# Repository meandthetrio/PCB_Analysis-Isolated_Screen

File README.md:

# PCB Analysis — two unrelated boards in one repo

| Board | Where | Status |
|---|---|---|
| **WavetableController ("Manifold")** — Trey's Daisy Seed synth controller, KiCad 9, fabbed twice | repo root (`WavetableController.*`, `Manifold_Gerb_LedFix/`, `analysis/`) | review complete, rev-2 planning |
| **ProtoBuild1 ("Rev K iron block")** — Quad Eight project, tuned-inductor all-pass "iron" saturation stage, KiCad 10, not yet fabbed | [`boards/ProtoBuild1/`](boards/ProtoBuild1/README.md) | review complete (2026-11-07) |

The two products share nothing but the tooling (`tools/`) and the six-pass checklist. Each has
its own `analysis/` with its own findings ledger (`F-nnn` for Manifold, `PB-F-nnn` for
ProtoBuild1). Everything below this line is about the WavetableController.

---

# PCB Analysis — WavetableController (Daisy Seed synth)

**Read this first.** This folder holds a completed design review of Trey's "WavetableController" board — an Electrosmith Daisy Seed–based wavetable synth controller, 2-layer, 165×102 mm, designed in KiCad 9. The board has been fabbed twice at JLCPCB and the physical boards mostly work. The analysis (all passes complete, 2026-08-13) found several real defects and produced a rev-2 plan.

**If you are Claude opening this fresh:** the authoritative output is [analysis/FINAL_REPORT.md](analysis/FINAL_REPORT.md) (tiered red flags + open questions for Trey), backed by the full findings ledger F-001…F-035 in [analysis/FINDINGS.md](analysis/FINDINGS.md). Do not re-derive anything before checking those. Methodology and which-file-is-truth rules are in [analysis/SOURCE_OF_TRUTH.md](analysis/SOURCE_OF_TRUTH.md).

## Folder contents

| Path | What it is |
|---|---|
| `WavetableController.kicad_pro` / `.kicad_sch` / `.kicad_pcb` | KiCad 9 design files, sent by Trey piecemeal (see provenance below) |
| `Manifold_Gerb_LedFix/` | The Gerbers + drill files actually sent to JLCPCB ("LedFix" round, 2nd proto). **Fab truth for copper.** |
| `ManifoldRe_BOM_NEW - Excel Format.xls` | JLCPCB-format BOM |
| `analysis/` | The full review: FINAL_REPORT, findings ledger, SOURCE_OF_TRUTH, PASS1–6 reports, REV2 OLED plan, routing CSVs extracted from Gerbers, board SVG, parser script. Has its own [README](analysis/README.md) index. |
| `screen mounting solution.md` | Mechanical mounting guide for the rev-2 Crystalfontz CFAL12864G-024W COG OLED (tape+gasket sandwich, plus 3D-printed bezel alternative) |

## Critical provenance warning

Trey sent files reluctantly and in stages: Gerbers+BOM first, then .pro/.sch, then the .kicad_pcb last. File mtimes are transfer times, not edit times. The `.kicad_pcb` in this folder matches the LedFix Gerbers ~97% **but contains NO GND pour** (only 5 keepout zones), while the fabbed B.Cu Gerber has a 164×100 mm filled pour covering 44/63 GND pads. It is a stale/wrong version — **never regenerate Gerbers from this copy.** Standing ask: get Trey's real working .kicad_pcb (the one that shows a filled B.Cu pour when opened). Where sch and pcb disagree (e.g. LED2 wiring), the pcb matches the fabbed boards, so the schematic is the outlier.

## Headline findings (details + evidence in analysis/)

- **Encoder push-buttons dead** — ENCL_CLICK / ENCR_CLICK have zero copper in the Gerbers (floating inputs; ENCR lands on a 3.3V-only Daisy pin). Fab-confirmed.
- **RGB LEDs triple-broken** — LED1/LED2 (CLS6B-FKW) are unplaced (missing from BOM, though the paste stencil expects them), reverse-biased via 300Ω to +9V_FILT (never light either polarity), and three LED pins sit on Daisy's 3.3V-only pins 24/25/30.
- **I2C has zero pull-ups in-design** — the ~203 mm bus relies entirely on the OLED module's onboard pull-ups (open question F-027 for Trey).
- **Duplicate refdes R21** — a layout-only 300Ω footprint at (170.1, 84.8) bridges /OLED_HOT–/+3V3_D in parallel with FB4 (Trey's noise-debug hack, on physical boards, not in schematic). Pick-and-place would put 300Ω where the 10Ω OLED damper belongs; breaks BOM/CPL matching.
- **0.1 mm traces board-wide** — exactly AT JLCPCB's 2-layer 1oz minimum (not below it), zero margin; carries the +3V3_D rail, I2C, SD, MIDI, USB. Recommend 0.2–0.25 mm. DRC min_track_width is 0.0 in the .kicad_pro, so KiCad won't flag them.
- **BOM refdes mismatch** — BOM's S1/S2 don't exist in the schematic (real refs are TAC_SWITCH_1/2, TAC_SHIFT_L1/R1 — note: underscore refs escape `[A-Z]+[0-9]+` regexes).
- 3 marginal fab violations (MK1 annular ring, P2 NPTH clearance, SW1 edge copper — the last is a deliberate notch, accepted). Power design: USB-C is data-only by design; 9V barrel → Schottky bridge → +9V_FILT (~8.3V).

**Open questions blocked on Trey:** F-014 (LED2 sch-vs-pcb, which is intended), F-027 (OLED module pull-up value), and the real .kicad_pcb with the GND pour.

## Rev-2 screen work (planning only, no design files changed)

[analysis/REV2_OLED_PLAN.md](analysis/REV2_OLED_PLAN.md): replace the two HiLetgo SSD1309 modules (boost-coil whine) with bare COG panels on 0.5 mm ZIF, independent I2C addresses 0x3C/0x3D. Two candidate panels:

- **Mono:** Crystalfontz CFAL12864G-024W (2.4", SSD1309) — needs 12.5–13.5V VCC, so a 15V adapter + ~13V LDO. Mounting solved in `screen mounting solution.md`.
- **Greyscale (user's preference):** no 2.42" greyscale panel exists anywhere. Best match is Raystar REX012864U / Winstar WEO012864U — 2.7" SSD1357, 16-level grey, VCC 8–10.5V (12V adapter + 10V LDO). **Unresolved geometry flag:** two 73 mm glasses = 146 mm side-by-side and conflict with the x≈165–200 audio-corridor keep-out. Fallback: stay mono, or 1.54" SSD1327.

Board changes either way: add 2.2k I2C pull-ups, remove J2/FB4/C14/C17/both R21s, use Daisy spare pads 22 & 28 for RES# and VCC_EN sequencing.

## Tooling notes

- **KiCad 9.0.9 (Linux / Claude Code on the web):** `kicad-cli` and the `pcbnew` Python module are on PATH. `.claude/hooks/session-start.sh` (a SessionStart hook) runs `tools/kicad_env_setup.sh` automatically in web sessions; run it by hand with `sudo tools/kicad_env_setup.sh` elsewhere. It installs the stock symbol/footprint libs and seed the user library tables (otherwise ERC/DRC add ~190 "library not found" warnings). `tools/kicad_check.sh [DIR BASENAME]` runs ERC, DRC, netlist, Gerber, SVG and PDF exports into `kicad_out/<basename>/` (git-ignored) as a smoke test; with no arguments it checks the WavetableController. `tools/kicad10_to_9.py SRC DST` makes a KiCad-9-loadable copy of a project that carries KiCad 10 library content (needed for ProtoBuild1).
- **Freerouting 2.4.1 autorouter** is installed by the same setup script (needs Java 25, installed alongside the system Java 21; `freerouting` wrapper on PATH runs it headless with analytics off). `tools/autoroute.py IN.kicad_pcb OUT.kicad_pcb [--passes N]` does DSN export → route → SES import. It temporarily renames the duplicate R21, because the Specctra exporter refuses boards with duplicate refdes (an independent confirmation of that finding). On the stale checked-in board, 2 passes took 53 unrouted connections to 5. Remaining lib warnings name Trey's private libs (`Retroactive_Custom_Parts`, `Jack_3.5mm_CUI_RetroactiveCustom`, `SOP-6_...(RetroactiveCustom)`), which only exist on his machine; footprints are embedded in the `.kicad_pcb`, so they are harmless. Note `pcbnew.LoadBoard(...).Zones()` returns 0 here because the 6 keepout zones live inside footprints, not at board level.
- On Trey's Mac, KiCad 10.0.5 lives at `/Applications/KiCad.app` (kicad-cli at `Contents/MacOS/kicad-cli`; brew cask fails without sudo).
- `analysis/gerber_analyze.py` is the Gerber parser/net-matcher that produced the routing CSVs. Other scratch scripts (pcb_parse.py, pcb_audit.py, DRC/ERC reports) lived in a session scratchpad and may be gone — regenerate from gerber_analyze.py patterns if needed.
- Net names in the routing CSVs are geometrically inferred (anchored at Daisy pins, 6/6 validated on LED nets), not authoritative; `island_*` = unidentified copper.

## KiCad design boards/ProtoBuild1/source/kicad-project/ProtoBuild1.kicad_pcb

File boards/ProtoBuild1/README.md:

# ProtoBuild1 — "Rev K iron block" (Quad Eight project)

**Unrelated to the Manifold / WavetableController board at the repo root.** This folder is a
self-contained design review of a second product that shares only the tooling and the
six-pass checklist.

**If you are Claude opening this fresh:** read `analysis/FINAL_REPORT.md` (tiered red flags +
questions for Trey), backed by the ledger `analysis/FINDINGS.md` (PB-F-001…PB-F-030). Do not
re-derive anything before checking those. Methodology and which-file-is-truth rules are in
`analysis/SOURCE_OF_TRUTH.md`.

## What the board is

A through-hole, 2-layer, 170 × 130 mm, ±15 V audio board: an inductor-saturation ("iron") colour stage, **not an EQ**. The coil sits in a
tuned second-order all-pass (OUT = 2P − D makes the magnitude flat, the phase rotates 360° through
the selected frequency) so the signal current, plus an optional DC magnetising bias, drives the
core into nonlinearity in a chosen band without changing the frequency response
(function derived from the netlist, see PASS5 and PB-F-032). Signal path: input jack → INPUT pot → NE5532 buffer → NE5532 DRIVE
stage (U1A inverting, U1B + U3B followers, 3 × 10 Ω share resistors) → node **D** → Q resistor
(SW2) → node **P** → tuning capacitor (SW1b) → node **X** → coil tap (SW1a) → RM10 tapped
inductor → 1 Ω sense (TP3) → GND. A discrete "Quad Eight" amplifier Q1–Q5 forms OUT = 2P − D,
then a bypass switch, OUTPUT pot, buffer and make-up stage drive the output jack. Q6 is a PNP
current source that can inject DC into X through SW4 to magnetise the core ("iron" bias).
Frequencies 100 / 200 / 400 / 800 Hz (188 / 94 / 47 / 23.5 mH against 13.3 / 6.8 / 3.3 / 1.68 µF).
All panel parts (3 pots, 1 dual pot, 2 rotary switches, 2 toggles) are off-board, wired to 18
screw-terminal blocks. The design has **not been fabricated yet**; JLCPCB is the intended fab.

## Folder contents

| Path | What it is |
|---|---|
| `source/` | The upload `ProtoBuild1-autorouted.zip` (7 Nov 2026) unpacked verbatim. `source/README-from-upload.md` is the author's own file list. |
| `source/kicad-project/` | `ProtoBuild1.kicad_sch`, `ProtoBuild1.kicad_pcb` (KiCad 8 file header, no zone fill), `ProtoBuild1-zones-filled-kicad10-format.kicad_pcb` (native KiCad 10 save, zone fill stored — **the file the Gerbers came from**), custom coil symbol + two footprints, project lib tables. |
| `source/gerbers/` | 7 Gerber layers + Excellon drill + job file, plotted by KiCad 10.0.8 on 2026-11-07. Candidate fab set, verified identical to the board file (Pass 0). |
| `source/reports/` | The author's KiCad 10 ERC / DRC text reports and the KiCad 10 netlist. |
| `source/ProtoBuild1-parts-list.xlsx` | Parts list with manufacturer numbers, DigiKey stock/prices (7 Nov 2026), and a "Trey has" column to fill in. |
| `analysis/` | The review: FINAL_REPORT, findings ledger, SOURCE_OF_TRUTH, pass plan, PASS0–6 reports, thresholds, extraction scripts, datasheet text extracts. |

## Opening the design files — read before you try

The `.kicad_sch` and `ProtoBuild1.kicad_pcb` are **not** KiCad 8 files despite their headers:
they are script-assembled from KiCad 10 library content. KiCad 10 opens them; **KiCad 9.0.9
refuses both with a parse error** (finding PB-F-001). In a KiCad 9 session run

```
tools/kicad10_to_9.py boards/ProtoBuild1/source/kicad-project kicad_out/pb1_conv
tools/kicad_check.sh kicad_out/pb1_conv ProtoBuild1
```

which writes a loadable *copy* (documented token strips only; copper and nets untouched, verified
by `analysis/scripts/gerber_vs_pcb.py`). Never edit the copy as if it were the design.

## Headline findings (details and evidence in analysis/)

- **The inductor is not connected** on the uploaded board: the coil footprint's 12 pins and its
  breakout row carry no net (PB-F-018). **Decision 2026-11-08:** the coil moves to a plug-in
  daughterboard; the main board needs a keyed 1 × 5 header for common + four taps (PB-F-031).
- **TO-92 pads break the JLCPCB annular-ring minimum** (0.15 mm vs 0.18 mm absolute minimum) on
  all 9 pads of Q1–Q3, because the 1.27 mm-pitch `TO-92_Inline` footprint was used while the BOM
  specifies 2.54 mm formed-lead parts (PB-F-006).
- **BOM is short two terminal blocks** (J13 3-pos and J17 2-pos, the coil-lead blocks); the "41
  terminal positions" wiring plan should be 46 (PB-F-020).
- **KiCad version trap** — files only open in KiCad 10; the upload README says 9 or 10
  (PB-F-001). DRC constraints are empty in the project file, so the author's "DRC 0" only
  reflects the 0.2 mm netclass (PB-F-002).
- **Q6 bias current source** can reach ~80 mA / ~0.85 W, above the BOM's "50 mA / 0.6 W", and
  its slip-on heatsink has ~6 mm of clearance where the BOM asks for 10 mm (PB-F-015, PB-F-023).
- Copper, netlist and Gerbers are mutually consistent (100 % segment match, 57/57 nets), ERC has
  zero errors in KiCad 9 and 10, polarities and transistor pinouts all check out against the
  datasheets, every terminal block faces outward at an edge, and the tuning arithmetic lands on
  100.7 / 199 / 404 / 801 Hz.

**Open questions for Trey:** the coil's actual pin layout (Don-Audio drawing), whether the
mounting holes should bond to chassis ground, heatsink orientation on Q6, and which KiCad
version the working files will live in.

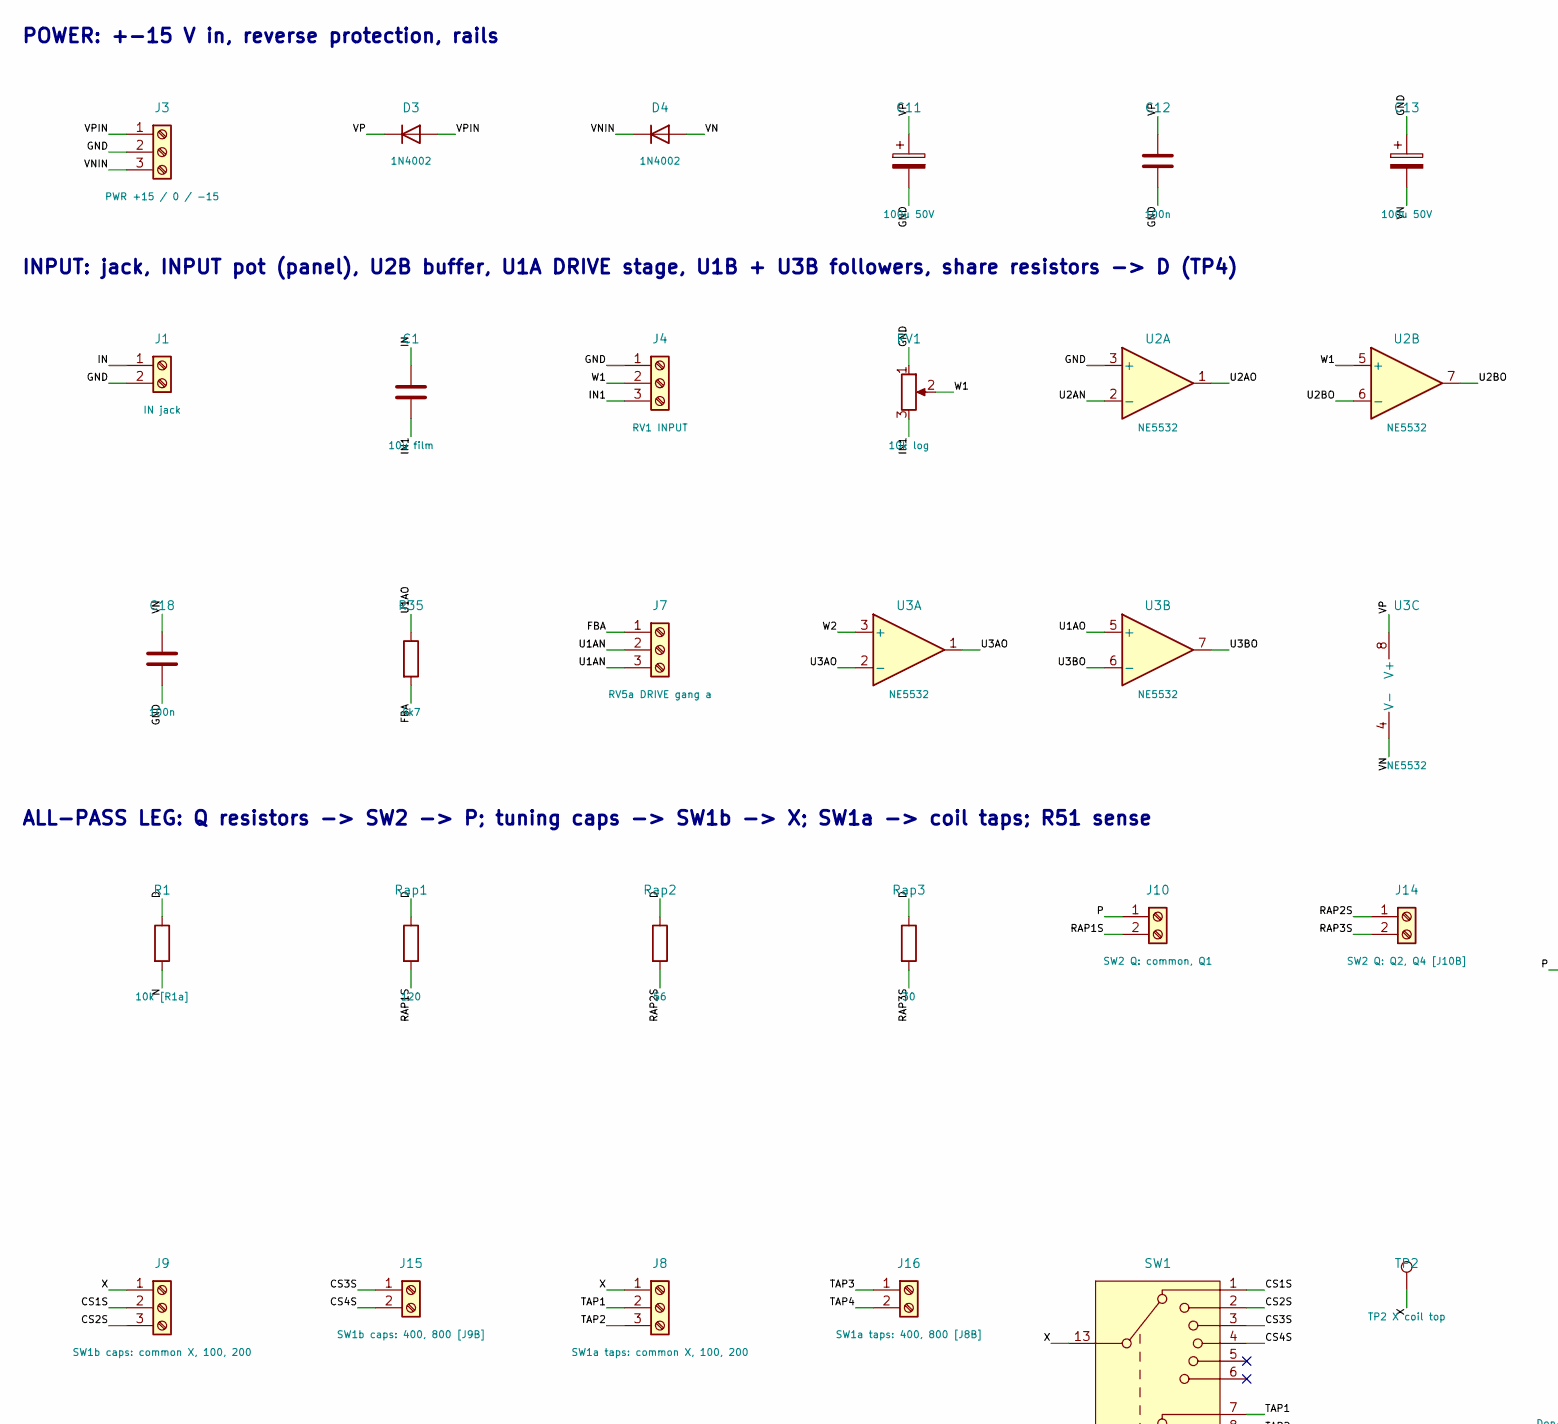
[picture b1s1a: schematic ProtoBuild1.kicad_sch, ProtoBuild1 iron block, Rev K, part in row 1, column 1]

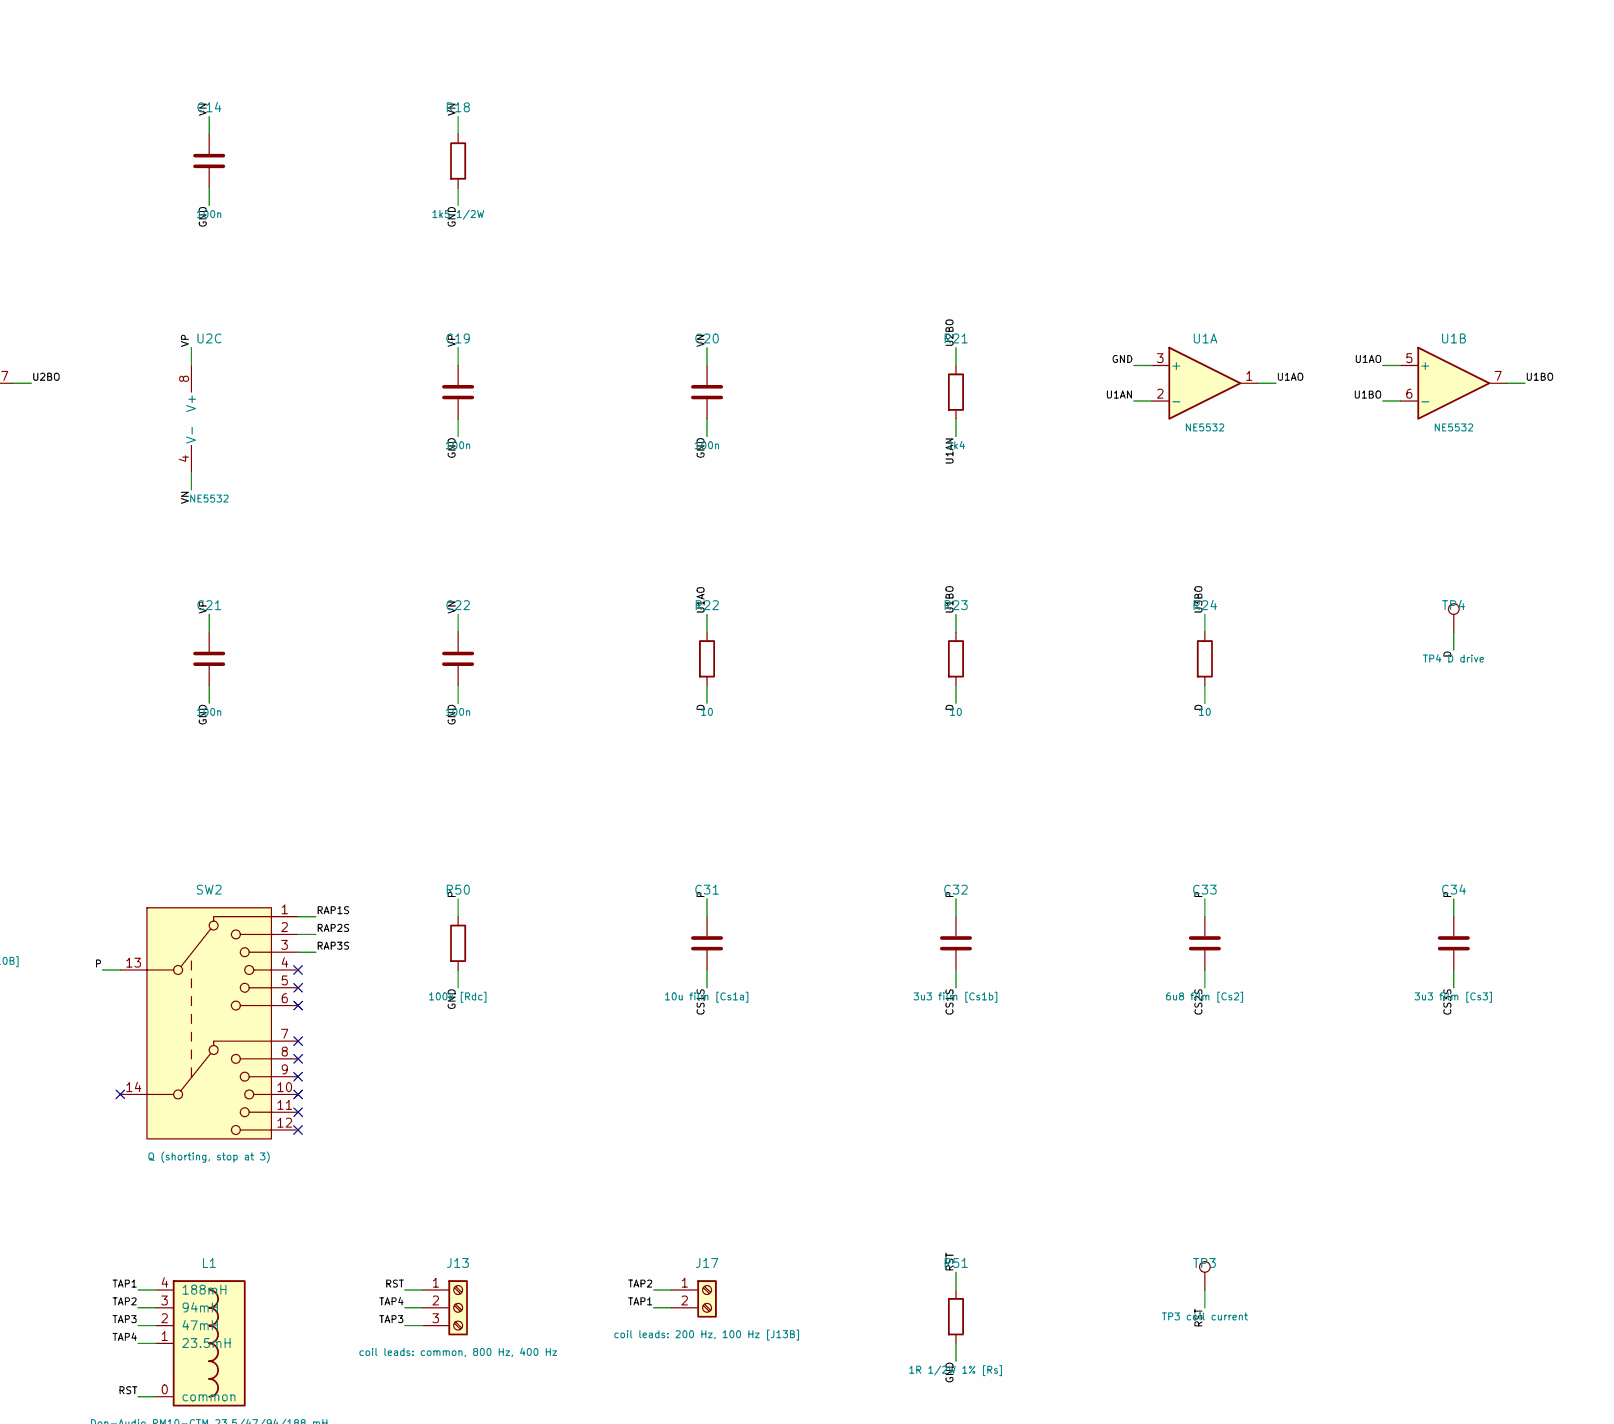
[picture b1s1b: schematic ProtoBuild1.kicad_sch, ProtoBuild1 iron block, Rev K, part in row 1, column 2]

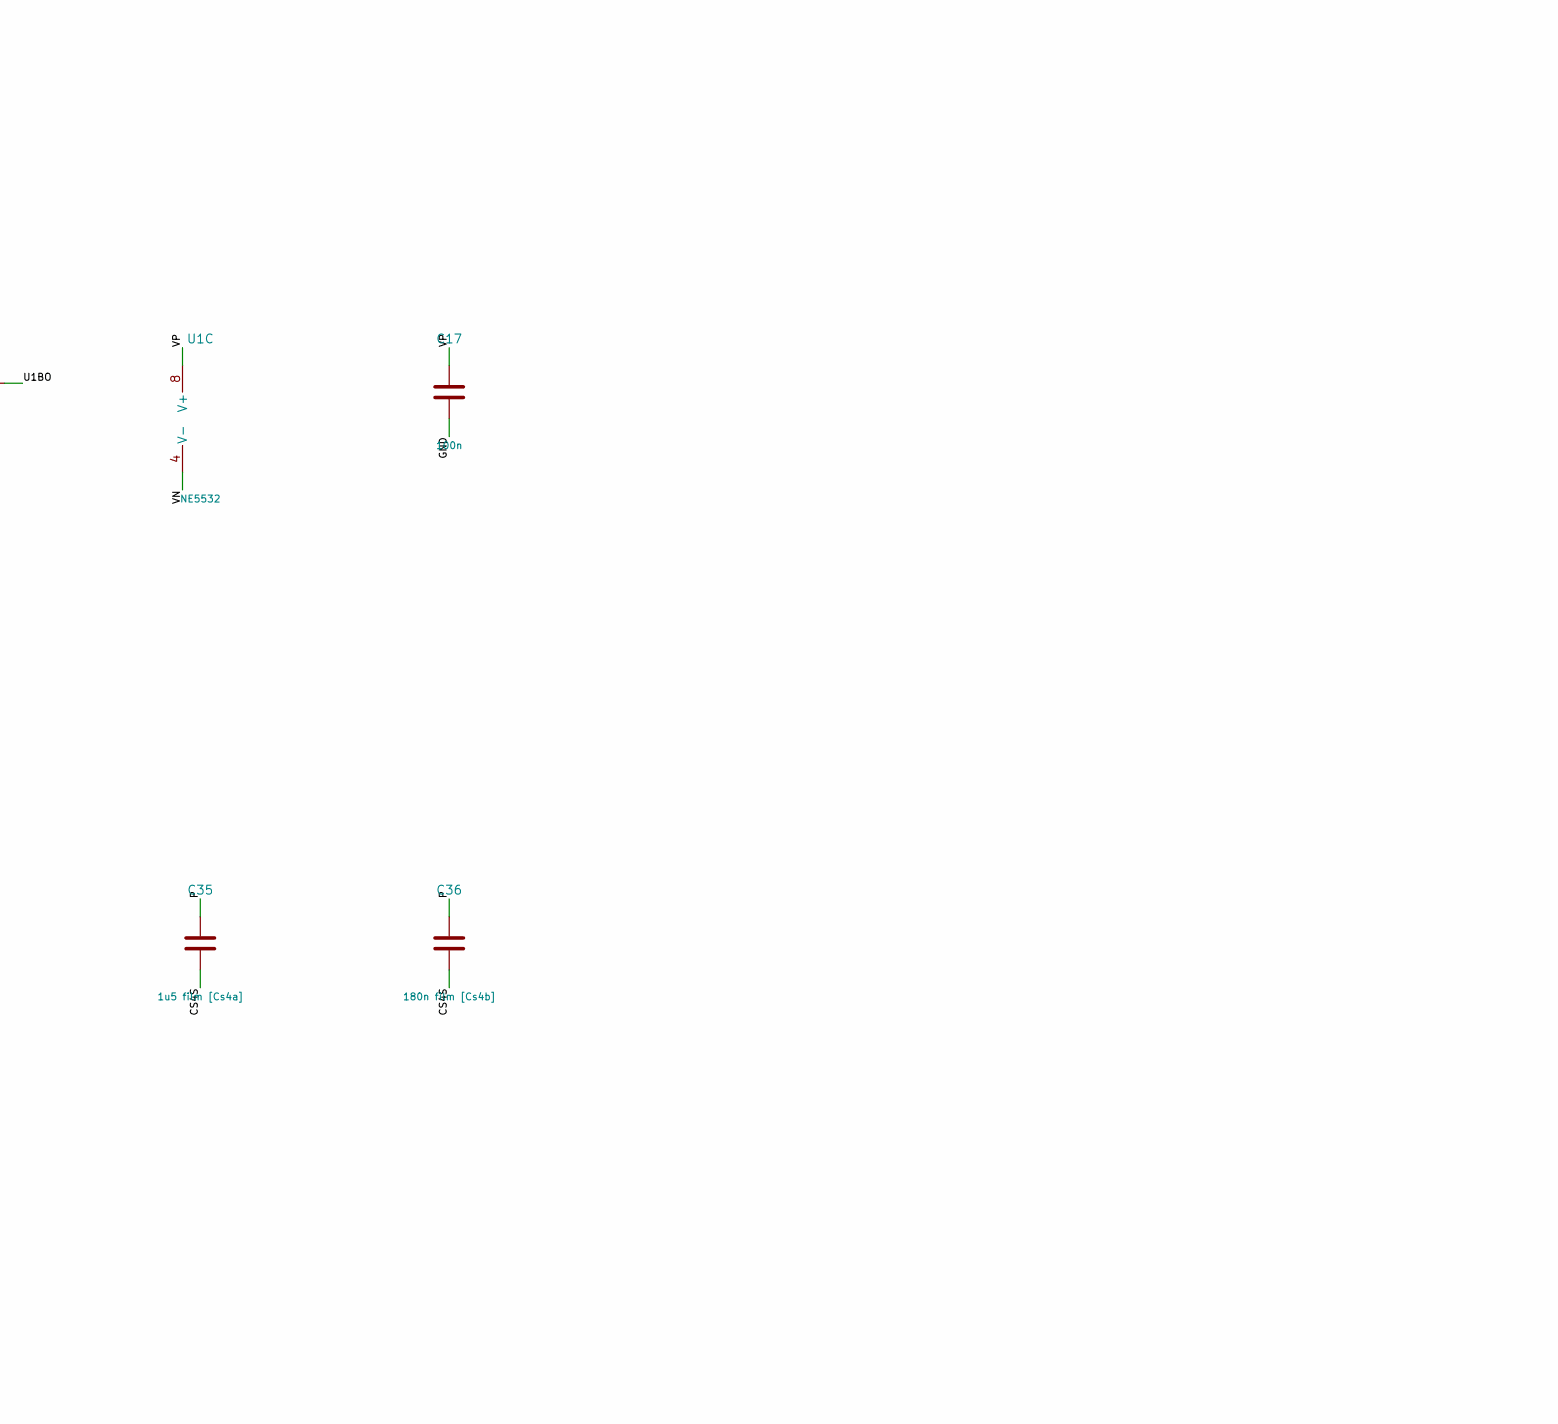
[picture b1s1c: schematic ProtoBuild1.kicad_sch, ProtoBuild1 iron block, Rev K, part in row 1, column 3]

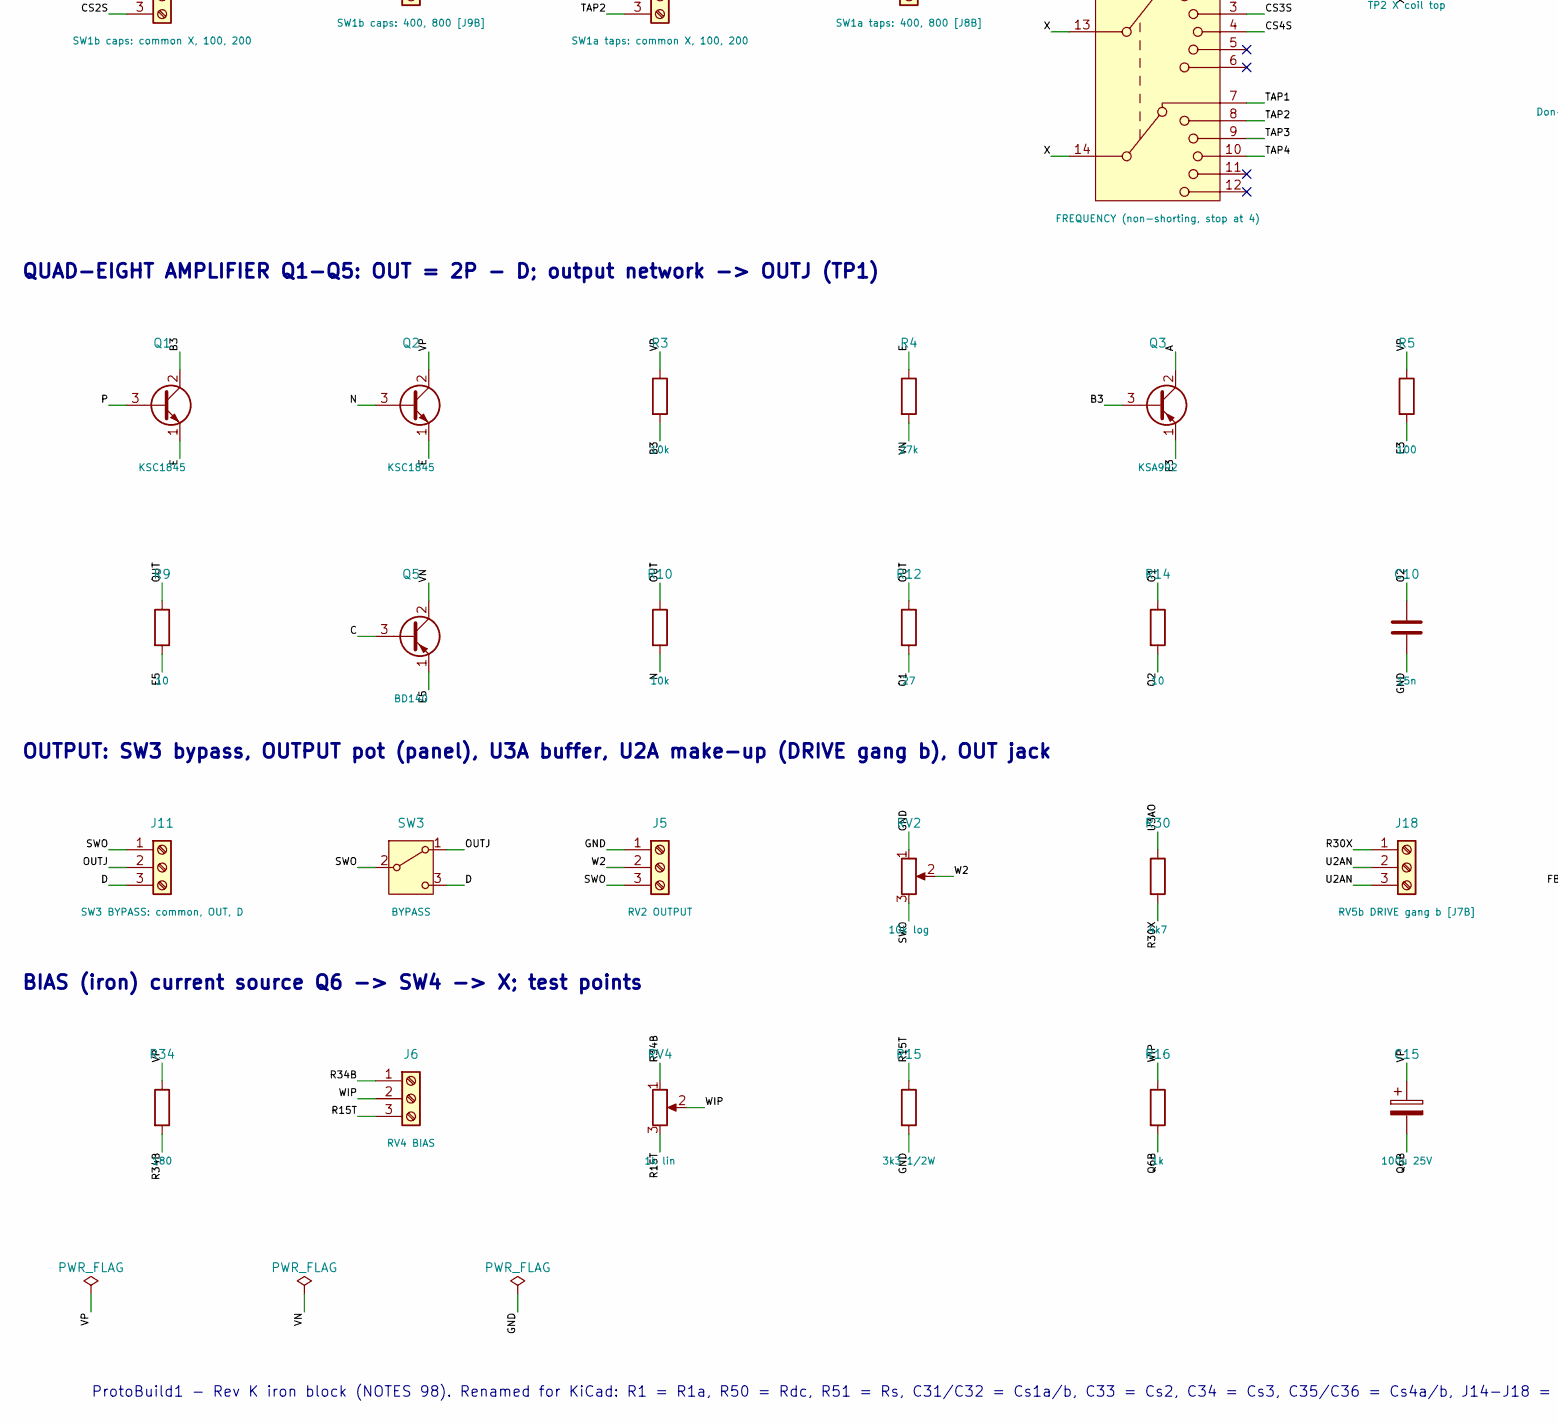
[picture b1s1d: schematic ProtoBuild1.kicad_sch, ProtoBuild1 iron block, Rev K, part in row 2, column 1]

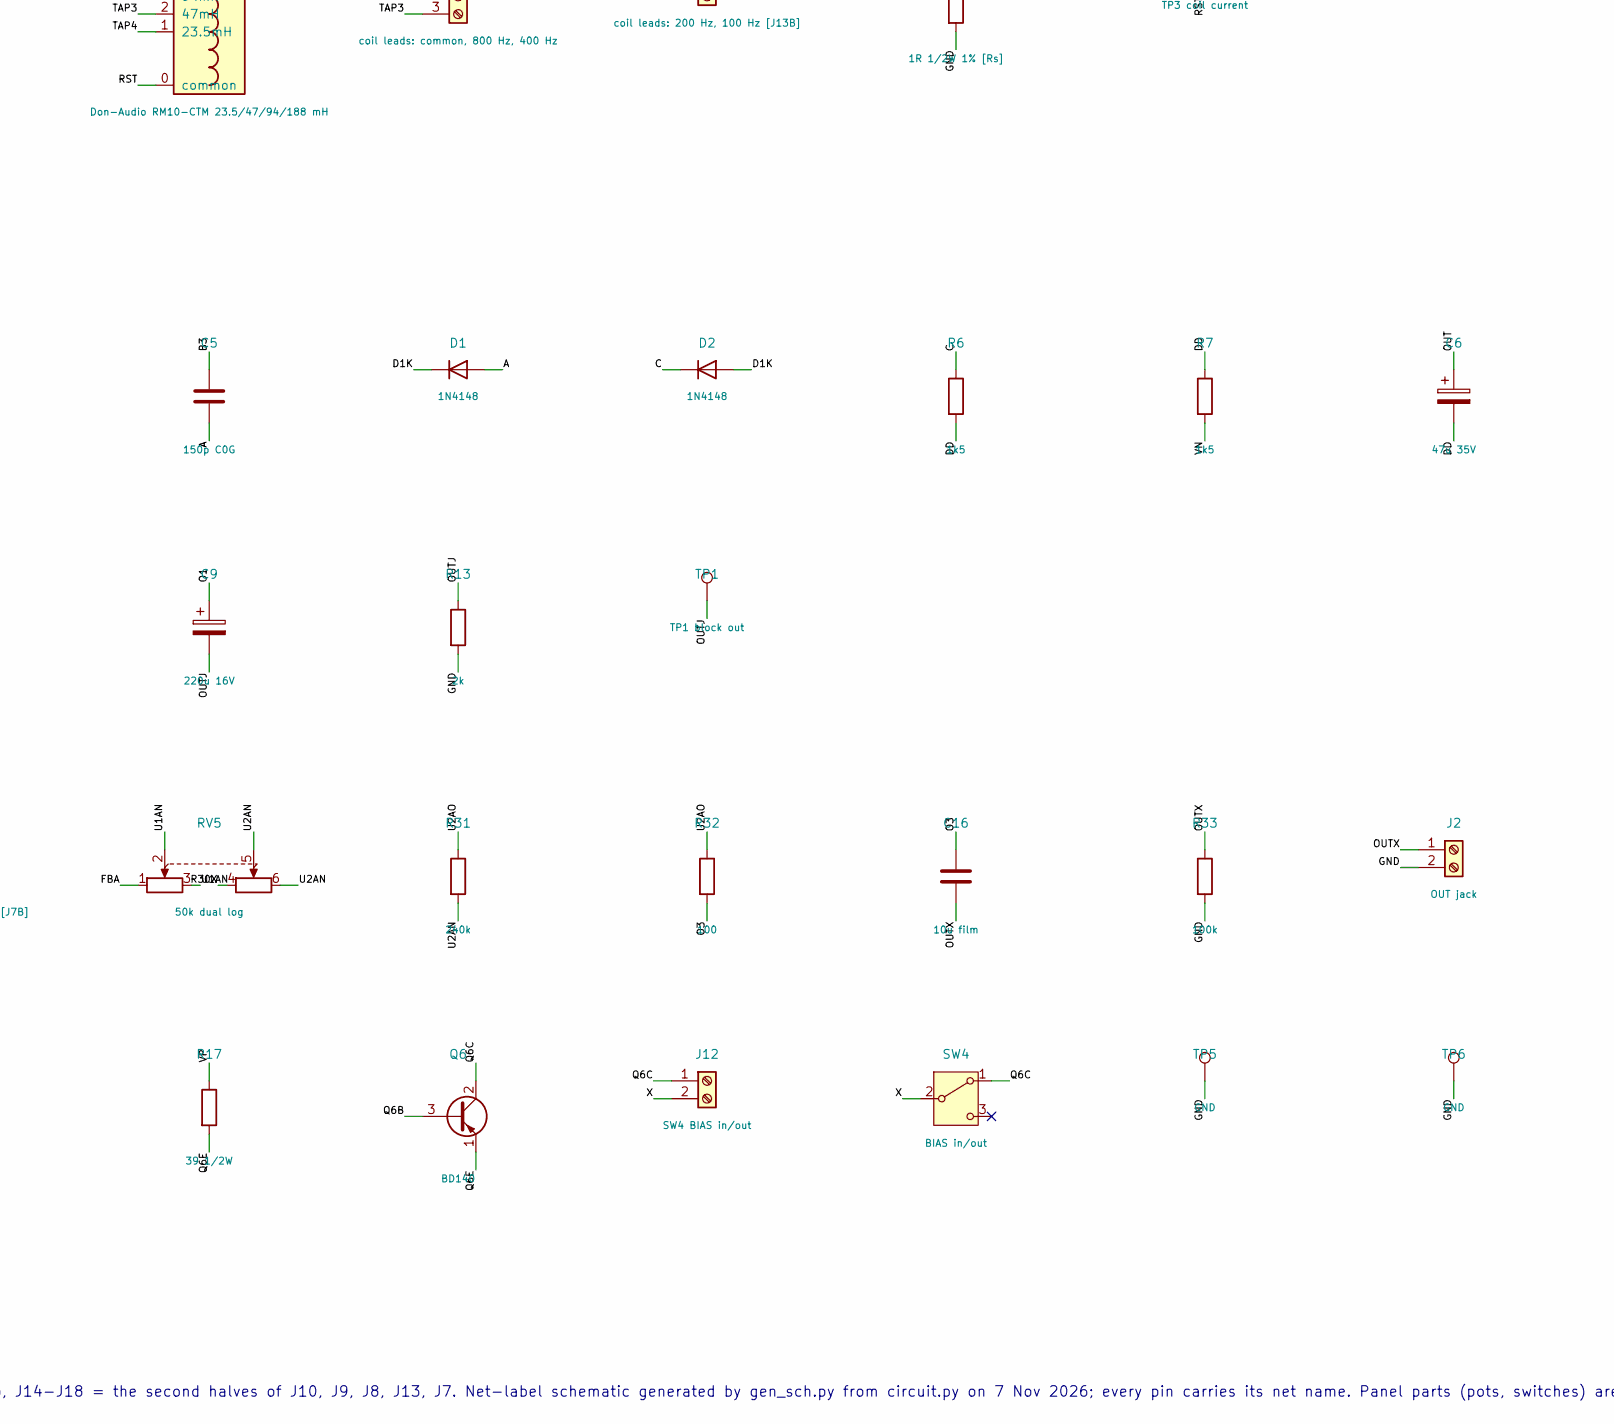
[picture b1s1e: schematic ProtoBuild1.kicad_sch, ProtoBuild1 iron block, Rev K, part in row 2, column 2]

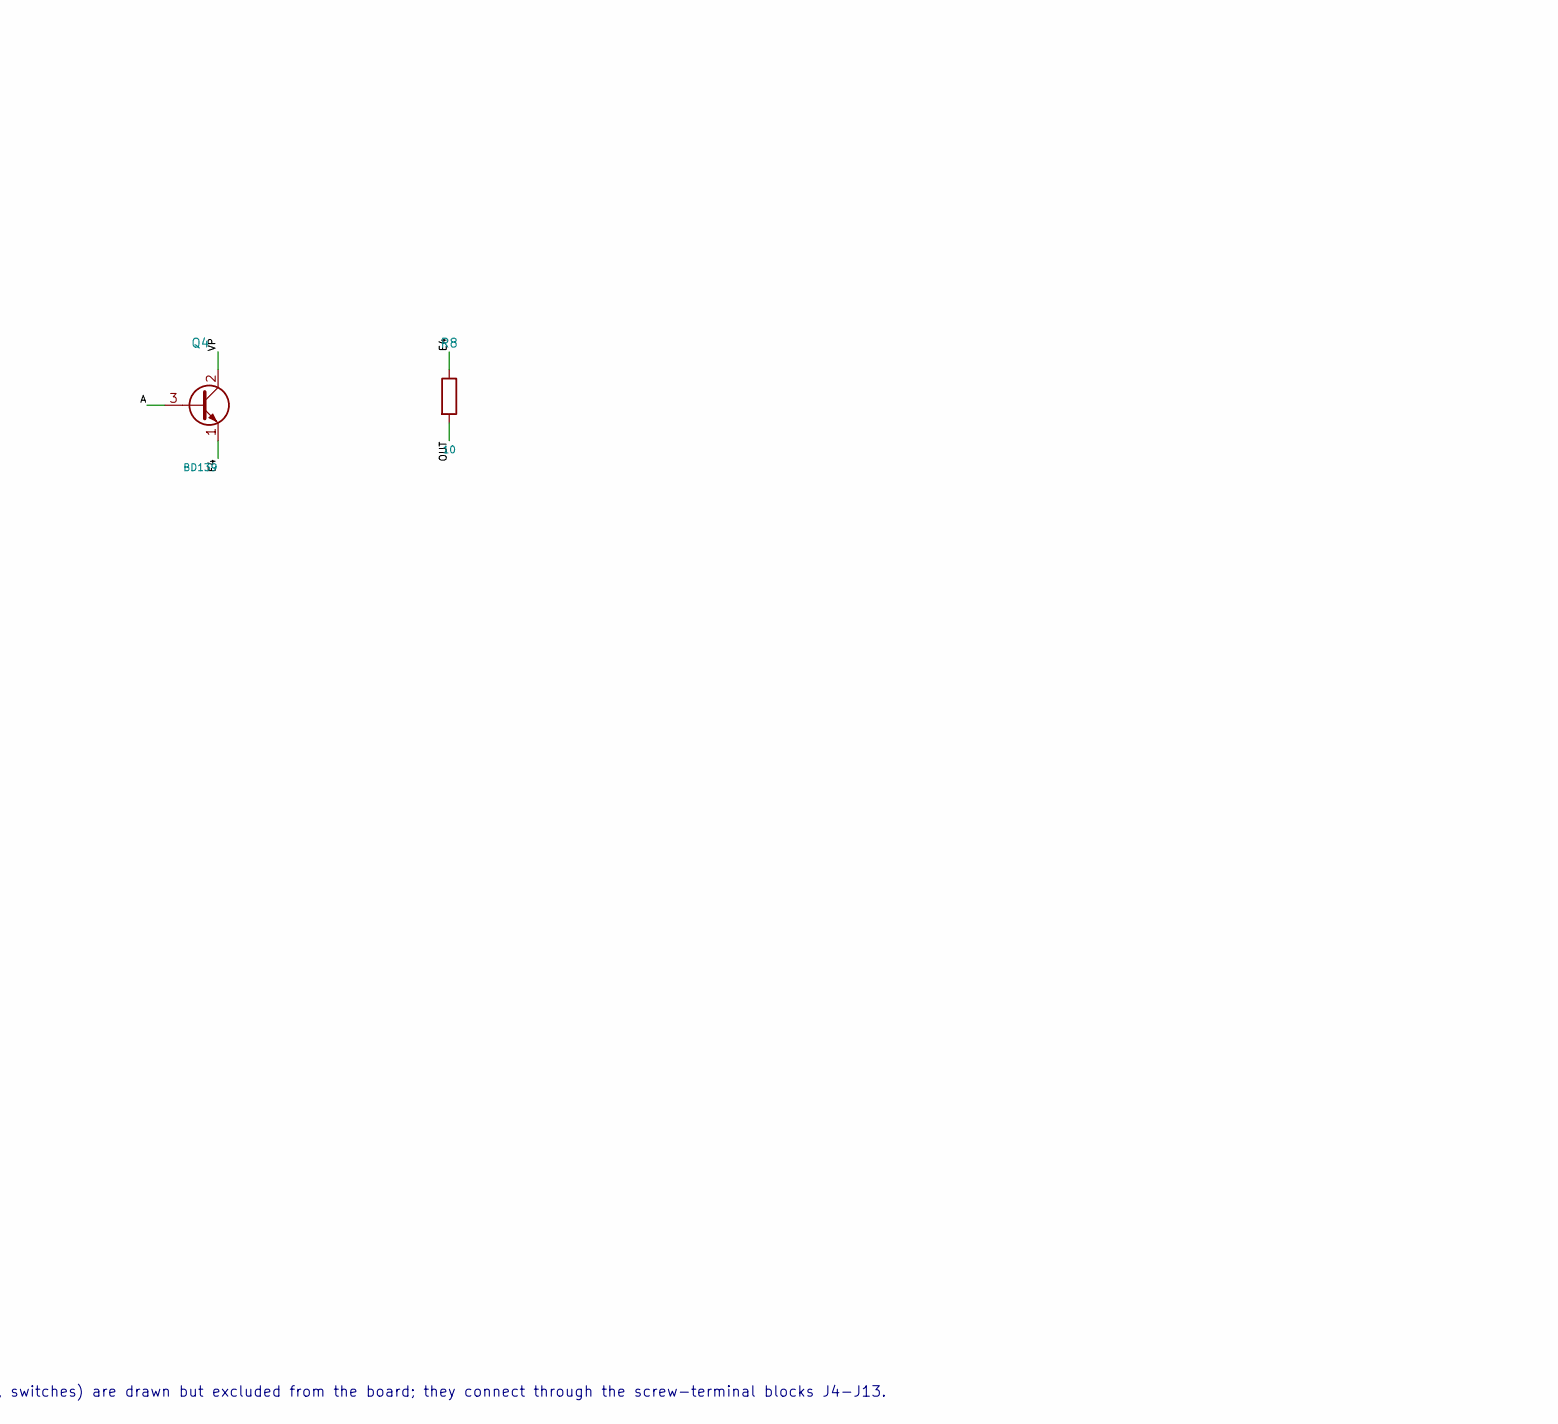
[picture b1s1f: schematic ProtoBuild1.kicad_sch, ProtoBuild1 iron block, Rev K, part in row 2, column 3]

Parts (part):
C1, C16: 10u film; C_Rect_L26.5mm_W11.5mm_P22.50mm_MKS4; MPN ECQ-E1106KF
C5: 150p C0G; C_Disc_D3.0mm_W1.6mm_P2.50mm; MPN K151J15C0GF5TL2
C6: 47u 35V; CP_Radial_D6.3mm_P2.50mm; MPN EEU-FM1V470
C9: 220u 16V; CP_Radial_D8.0mm_P3.50mm; MPN UPW1C221MPD
C10: 15n; C_Rect_L7.2mm_W2.5mm_P5.00mm; MPN B32529C0153J000
C11, C13: 100u 50V; CP_Radial_D8.0mm_P3.50mm; MPN UPW1H101MPD
C12, C14, C17, C18, C19, C20, C21, C22: 100n; C_Rect_L7.2mm_W2.5mm_P5.00mm; MPN B32529C0104J000
C15: 100u 25V; CP_Radial_D6.3mm_P2.50mm; MPN UPW1E101MED
C31: 10u film [Cs1a]; C_Rect_L26.5mm_W11.5mm_P22.50mm_MKS4; MPN ECQ-E1106KF
C32: 3u3 film [Cs1b]; C_Rect_L18.0mm_W9.0mm_P15.00mm_FKS3_FKP3; MPN ECQ-E1335KF
C33: 6u8 film [Cs2]; C_Rect_L26.5mm_W8.5mm_P22.50mm_MKS4; MPN ECQ-E1685KF
C34: 3u3 film [Cs3]; C_Rect_L18.0mm_W9.0mm_P15.00mm_FKS3_FKP3; MPN ECQ-E1335KF
C35: 1u5 film [Cs4a]; C_Rect_L18.0mm_W6.0mm_P15.00mm_FKS3_FKP3; MPN ECQ-E1155KF
C36: 180n film [Cs4b]; C_Rect_L11.5mm_W5.0mm_P10.00mm_MKT; MPN ECQ-E2184KF
D1, D2: 1N4148; D_DO-35_SOD27_P7.62mm_Horizontal; MPN 1N4148
D3, D4: 1N4002; D_DO-41_SOD81_P10.16mm_Horizontal; MPN 1N4002G
J1: IN jack; TerminalBlock_Phoenix_MKDS-1,5-2-5.08_1x02_P5.08mm_Horizont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; MPN Phoenix 1715022
J2: OUT jack; TerminalBlock_Phoenix_MKDS-1,5-2-5.08_1x02_P5.08mm_Horizont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; MPN Phoenix 1715022
J3: PWR +15 / 0 / -15; TerminalBlock_Phoenix_MKDS-1,5-3-5.08_1x03_P5.08mm_Horizont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; MPN Phoenix 1715035
J4: RV1 INPUT; TerminalBlock_Phoenix_MKDS-1,5-3-5.08_1x03_P5.08mm_Horizont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; MPN Phoenix 1715035
J5: RV2 OUTPUT; TerminalBlock_Phoenix_MKDS-1,5-3-5.08_1x03_P5.08mm_Horizont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; MPN Phoenix 1715035
J6: RV4 BIAS; TerminalBlock_Phoenix_MKDS-1,5-3-5.08_1x03_P5.08mm_Horizont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; MPN Phoenix 1715035
J7: RV5a DRIVE gang a; TerminalBlock_Phoenix_MKDS-1,5-3-5.08_1x03_P5.08mm_Horizont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; MPN Phoenix 1715035
J8: SW1a taps: common X, 100, 200; TerminalBlock_Phoenix_MKDS-1,5-3-5.08_1x03_P5.08mm_Horizont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; MPN Phoenix 1715035
J9: SW1b caps: common X, 100, 200; TerminalBlock_Phoenix_MKDS-1,5-3-5.08_1x03_P5.08mm_Horizont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; MPN Phoenix 1715035
J10: SW2 Q: common, Q1; TerminalBlock_Phoenix_MKDS-1,5-2-5.08_1x02_P5.08mm_Horizont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; MPN Phoenix 1715022
J11: SW3 BYPASS: common, OUT, D; TerminalBlock_Phoenix_MKDS-1,5-3-5.08_1x03_P5.08mm_Horizont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; MPN Phoenix 1715035
J12: SW4 BIAS in/out; TerminalBlock_Phoenix_MKDS-1,5-2-5.08_1x02_P5.08mm_Horizont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; MPN Phoenix 1715022
J13: coil leads: common, 800 Hz, 400 Hz; TerminalBlock_Phoenix_MKDS-1,5-3-5.08_1x03_P5.08mm_Horizont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; MPN Phoenix 1715035
J14: SW2 Q: Q2, Q4 [J10B]; TerminalBlock_Phoenix_MKDS-1,5-2-5.08_1x02_P5.08mm_Horizont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; MPN Phoenix 1715022
J15: SW1b caps: 400, 800 [J9B]; TerminalBlock_Phoenix_MKDS-1,5-2-5.08_1x02_P5.08mm_Horizont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; MPN Phoenix 1715022
J16: SW1a taps: 400, 800 [J8B]; TerminalBlock_Phoenix_MKDS-1,5-2-5.08_1x02_P5.08mm_Horizont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; MPN Phoenix 1715022
J17: coil leads: 200 Hz, 100 Hz [J13B]; TerminalBlock_Phoenix_MKDS-1,5-2-5.08_1x02_P5.08mm_Horizont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; MPN Phoenix 1715022
J18: RV5b DRIVE gang b [J7B]; TerminalBlock_Phoenix_MKDS-1,5-3-5.08_1x03_P5.08mm_Horizont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; MPN Phoenix 1715035
L1: Don-Audio RM10-CTM 23.5/47/94/188 mH; RM10_corner_12P_breakout; MPN Don-Audio RM10-CTM
Q1, Q2: KSC1845; TO-92_Inline; MPN KSC1845FTA
Q3: KSA992; TO-92_Inline; MPN KSA992FTA
Q4: BD139; TO-126-3_Vertical; MPN BD139G
Q5, Q6: BD140; TO-126-3_Vertical; MPN BD140G
R1: 10k [R1a]; R_Axial_DIN0207_L6.3mm_D2.5mm_P10.16mm_Horizontal; MPN MFR-25FBF52-10K
R3, R10: 10k; R_Axial_DIN0207_L6.3mm_D2.5mm_P10.16mm_Horizontal; MPN MFR-25FBF52-10K
R4: 27k; R_Axial_DIN0207_L6.3mm_D2.5mm_P10.16mm_Horizontal; MPN MFR-25FBF52-27K
R5, R32: 100; R_Axial_DIN0207_L6.3mm_D2.5mm_P10.16mm_Horizontal; MPN MFR-25FBF52-100R
R6, R7: 1k5; R_Axial_DIN0207_L6.3mm_D2.5mm_P10.16mm_Horizontal; MPN MFR-25FBF52-1K5
R8, R9, R14, R22, R23, R24: 10; R_Axial_DIN0207_L6.3mm_D2.5mm_P10.16mm_Horizontal; MPN MFR-25FBF52-10R
R12: 27; R_Axial_DIN0207_L6.3mm_D2.5mm_P10.16mm_Horizontal; MPN MFR-25FBF52-27R
R13: 2k; R_Axial_DIN0207_L6.3mm_D2.5mm_P10.16mm_Horizontal; MPN MFR-25FBF52-2K
R15: 3k3 1/2W; R_Axial_DIN0309_L9.0mm_D3.2mm_P12.70mm_Horizontal; MPN MFR50SFTE52-3K3
R16: 1k; R_Axial_DIN0207_L6.3mm_D2.5mm_P10.16mm_Horizontal; MPN MFR-25FBF52-1K
R17: 39 1/2W; R_Axial_DIN0309_L9.0mm_D3.2mm_P12.70mm_Horizontal; MPN MFR50SFTE52-39R
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
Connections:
A: C5.2, D1.2 (A), Q3.2 (C), Q4.3 (B)
B3: C5.1, Q1.2 (C), Q3.3 (B), R3.2
C: D2.1 (K), Q5.3 (B), R6.1
CS1S: C31.2, C32.2, J9.2, SW1.1
CS2S: C33.2, J9.3, SW1.2
CS3S: C34.2, J15.1, SW1.3
CS4S: C35.2, C36.2, J15.2, SW1.4
D: J11.3, R1.1, R22.2, R23.2, R24.2, Rap1.1, Rap2.1, Rap3.1, SW3.3 (C), TP4.1
D1K: D1.1 (K), D2.2 (A)
DD: C6.2, R6.2, R7.1
E: Q1.1 (E), Q2.1 (E), R4.1
E3: Q3.1 (E), R5.2
E4: Q4.1 (E), R8.1
E5: Q5.1 (E), R9.2
FBA: J7.1, R35.2, RV5.1
GND: C10.2, C11.2, C12.2, C13.1, C14.2, C17.2, C18.2, C19.2, C20.2, C21.2, C22.2, J1.2, J2.2, J3.2, J4.1, J5.1, R13.2, R15.2, R18.2, R33.2, R50.2, R51.2, RV1.1, RV2.1, TP5.1, TP6.1, U1.3 (+), U2.3 (+)
IN: C1.1, J1.1
IN1: C1.2, J4.3, RV1.3
N: Q2.3 (B), R1.2, R10.2
O1: C9.1, R12.2, R14.1
O2: C10.1, R14.2
O3: C16.1, R32.2
OUT: C6.1, R8.2, R9.1, R10.1, R12.1
OUTJ: C9.2, J11.2, R13.1, SW3.1 (A), TP1.1
OUTX: C16.2, J2.1, R33.1
P: C31.1, C32.1, C33.1, C34.1, C35.1, C36.1, J10.1, Q1.3 (B), R50.1, SW2.13
Q6B: C15.2, Q6.3 (B), R16.2
Q6C: J12.1, Q6.2 (C), SW4.1 (A)
Q6E: Q6.1 (E), R17.2
R15T: J6.3, R15.1, RV4.3
R30X: J18.1, R30.2, RV5.4
R34B: J6.1, R34.2, RV4.1
RAP1S: J10.2, Rap1.2, SW2.1
RAP2S: J14.1, Rap2.2, SW2.2
RAP3S: J14.2, Rap3.2, SW2.3
RST: J13.1, L1.0 (common), R51.1, TP3.1
SWO: J5.3, J11.1, RV2.3, SW3.2 (B)
TAP1: J8.2, J17.2, L1.4 (188mH), SW1.7
TAP2: J8.3, J17.1, L1.3 (94mH), SW1.8
TAP3: J13.3, J16.1, L1.2 (47mH), SW1.9
TAP4: J13.2, J16.2, L1.1 (23.5mH), SW1.10
U1AN: J7.2, J7.3, R21.2, RV5.2, RV5.3, U1.2 (-)
U1AO: R22.1, R35.1, U1.1, U1.5 (+), U3.5 (+)
U1BO: R23.1, U1.6 (-), U1.7
U2AN: J18.2, J18.3, R31.2, RV5.5, RV5.6, U2.2 (-)
U2AO: R31.1, R32.1, U2.1
U2BO: R21.1, U2.6 (-), U2.7
U3AO: R30.1, U3.1, U3.2 (-)
U3BO: R24.1, U3.6 (-), U3.7
VN: C13.2, C14.1, C18.1, C20.1, C22.1, D4.2 (A), Q5.2 (C), R4.2, R7.2, R18.1, U1.4 (V-), U2.4 (V-), U3.4 (V-)
VNIN: D4.1 (K), J3.3
VP: C11.1, C12.1, C15.1, C17.1, C19.1, C21.1, D3.1 (K), Q2.2 (C), Q4.2 (C), R3.1, R5.1, R17.1, R34.1, U1.8 (V+), U2.8 (V+), U3.8 (V+)
VPIN: D3.2 (A), J3.1
W1: J4.2, RV1.2, U2.5 (+)
W2: J5.2, RV2.2, U3.3 (+)
WIP: J6.2, R16.1, RV4.2
X: J8.1, J9.1, J12.2, SW1.13, SW1.14, SW4.2 (B), TP2.1

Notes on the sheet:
POWER: +-15 V in, reverse protection, rails
INPUT: jack, INPUT pot (panel), U2B buffer, U1A DRIVE stage, U1B + U3B followers, share resistors -> D (TP4)
ALL-PASS LEG: Q resistors -> SW2 -> P; tuning caps -> SW1b -> X; SW1a -> coil taps; R51 sense
QUAD-EIGHT AMPLIFIER Q1-Q5: OUT = 2P - D; output network -> OUTJ (TP1)
OUTPUT: SW3 bypass, OUTPUT pot (panel), U3A buffer, U2A make-up (DRIVE gang b), OUT jack
BIAS (iron) current source Q6 -> SW4 -> X; test points
ProtoBuild1 - Rev K iron block (NOTES 98). Renamed for KiCad: R1 = R1a, R50 = Rdc, R51 = Rs, C31/C32 = Cs1a/b, C33 = Cs2, C34 = Cs3, C35/C36 = Cs4a/b, J14-J18 = the second halves of J10, J9, J8, J13, J7. Net-label schematic generated by gen_sch.py from circuit.py on 7 Nov 2026; every pin carries it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

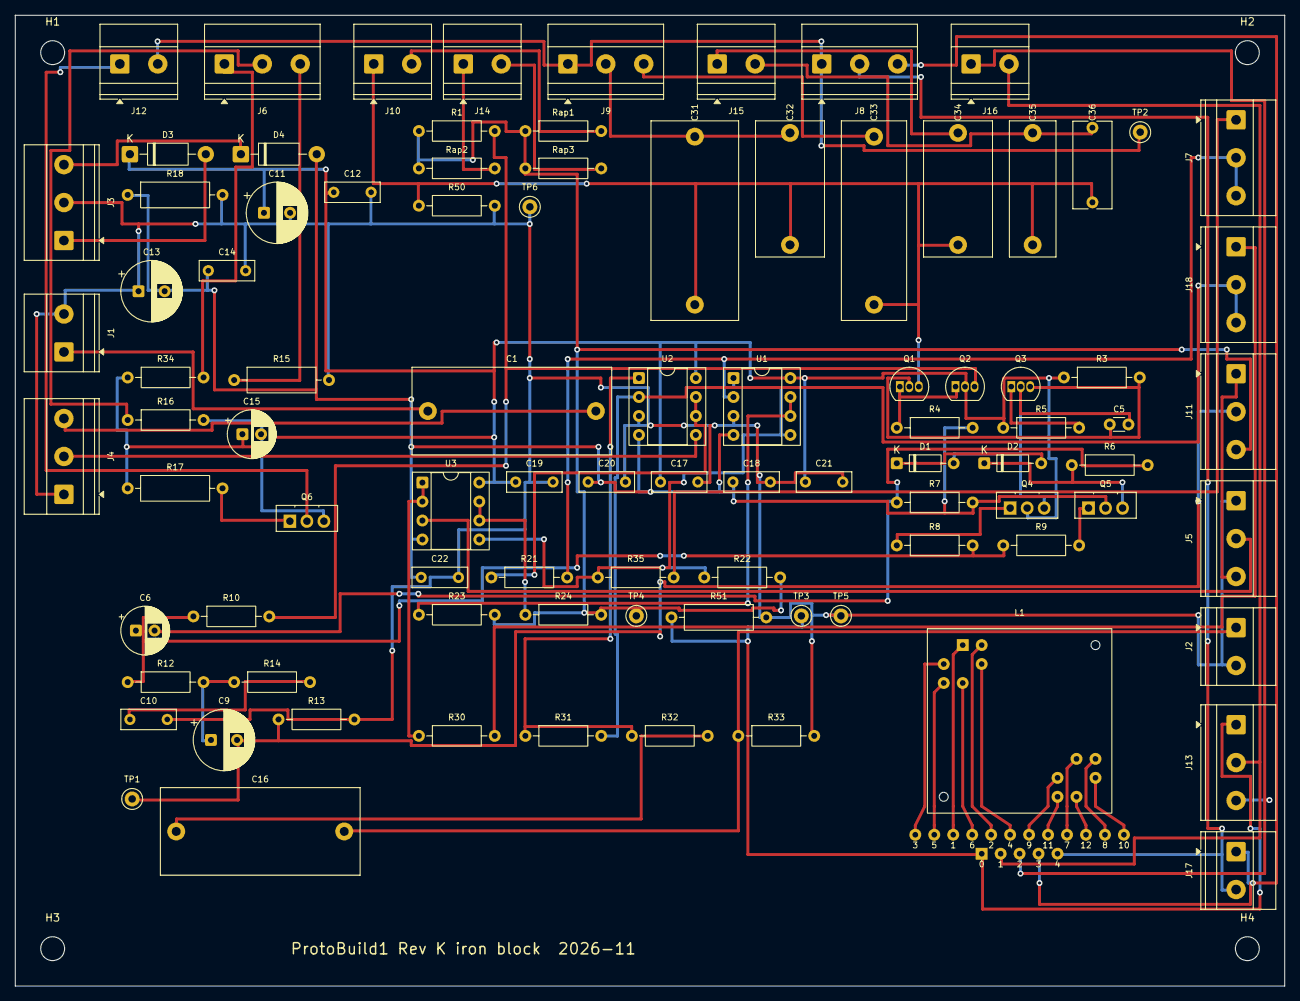
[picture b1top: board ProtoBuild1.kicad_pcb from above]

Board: 2 copper layers, 170.0 x 130.0 mm, 96 parts (0 on the bottom side), 57 nets.

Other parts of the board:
H1, H2, H3, H4: MountingHole_3.2mm_M3
